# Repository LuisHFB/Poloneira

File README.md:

# Poloneira
Trabalho da esteira seletora de peças da aula de Acionamentos e Sensores, Prof. Leandro Poloni.

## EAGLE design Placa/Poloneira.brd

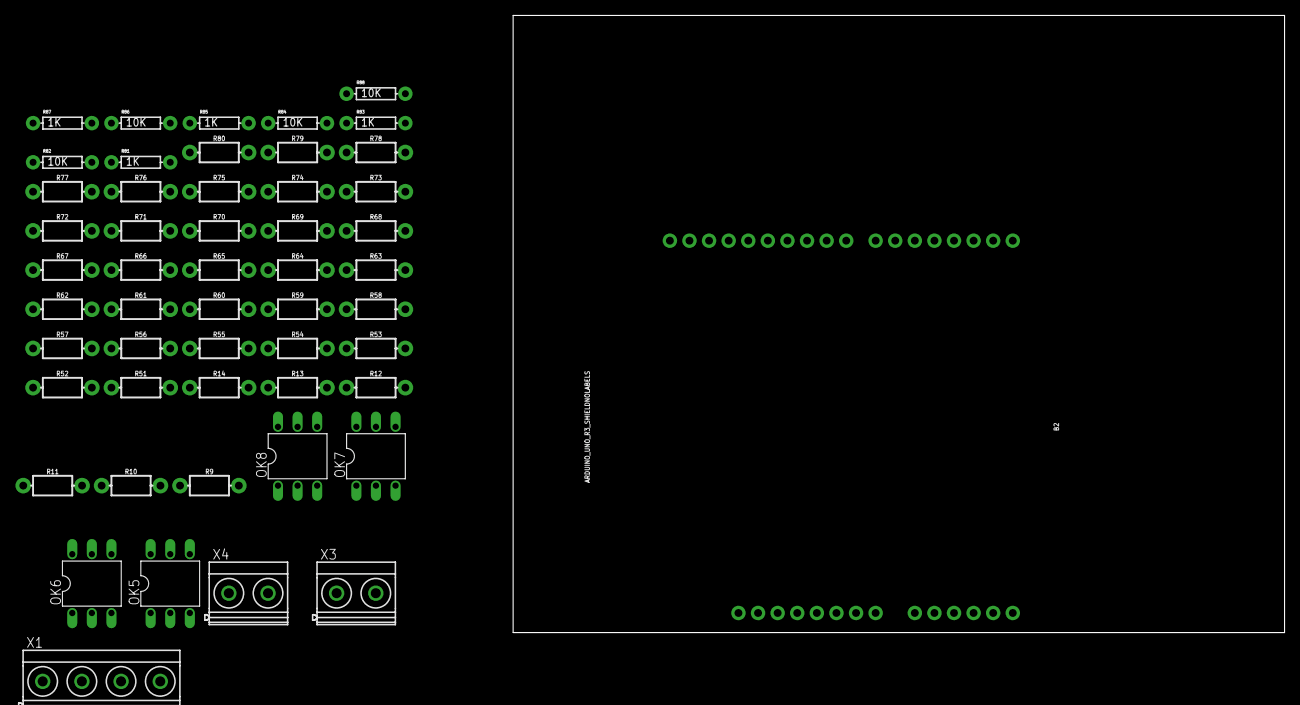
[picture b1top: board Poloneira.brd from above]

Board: 2 copper layers, 100.0 x 80.0 mm, 52 parts (0 on the bottom side), 15 nets, no tracks yet.

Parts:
B2: ARDUINO_UNO_R3_SHIELDNOLABELS; UNO_R3_SHIELD_NOLABELS
OK5, OK6, OK7, OK8: 4N25M; DIL06
R9, R10, R11, R12, R13, R14, R51, R52, R53, R54, R55, R56, R57, R58, R59, R60, R61, R62, R63, R64, R65, R66, R67, R68, R69, R70, R71, R72, R73, R74, R75, R76, R77, R78, R79, R80: AXIAL-0.3-KIT
R81, R83, R85, R87: 1K; AXIAL-0.3EZ
R82, R84, R86, R88: 10K; AXIAL-0.3EZ
X1: MKDSN1,5/4-5,08
X3, X4: MKDSN1,5/2-5,08

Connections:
+24V: R82.P$1, R84.P$1, R86.P$1, R88.P$1, X3.2
GND: OK5.2, OK5.4, OK6.2, OK6.4, OK7.2, OK7.4, OK8.2, OK8.4, R10.P$1, R12.P$1, R14.P$1, R52.P$1, R54.P$1, R56.P$1, R58.P$1, R60.P$1, R62.P$1, R64.P$1, R66.P$1, R68.P$1, R70.P$1, R72.P$1, R74.P$1, R76.P$1, R78.P$1, R80.P$1, X3.1, X4.2
unnamed: OK5.1, R81.P$1
unnamed: OK6.1, R83.P$1
unnamed: OK7.1, R85.P$1
unnamed: OK8.1, R87.P$1
unnamed: R81.P$2, R83.P$2, R85.P$2, R87.P$2
PISTAO1: OK5.5, R82.P$2, X1.1
PISTAO2: OK6.5, R84.P$2, X1.2
PISTAO3: OK7.5, R86.P$2, X1.3
PISTAO4: OK8.5, R88.P$2, X1.4
SENSA_5V: R13.P$2, R14.P$2
SENSB_5V: R9.P$2, R10.P$2, R51.P$2, R52.P$2, R53.P$2, R54.P$2, R55.P$2, R56.P$2, R57.P$2, R58.P$2, R59.P$2, R60.P$2, R61.P$2, R62.P$2, R63.P$2, R64.P$2, R65.P$2, R66.P$2, R67.P$2, R68.P$2, R69.P$2, R70.P$2, R71.P$2, R72.P$2, R73.P$2, R74.P$2, R75.P$2, R76.P$2, R77.P$2, R78.P$2, R79.P$2, R80.P$2
SENSB_24V: R9.P$1, R55.P$1, R57.P$1, R59.P$1, R61.P$1, R63.P$1, R65.P$1, R67.P$1, R69.P$1, R71.P$1, R73.P$1, R75.P$1, R77.P$1, R79.P$1
SENSM_5V: R11.P$2, R12.P$2

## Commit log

2018-10-31 Arquivos Eagle
    Arquivos BRD e SCH para placa
2018-11-06 05_11_2018
2018-11-09 09_11_2018
2018-11-09 09_11_2018_(2)
2018-11-12 12_11_2018_(1)
2018-11-12 Agora Funfa
2018-11-12 Agora sim

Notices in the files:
parts and their libraries:
SparkFun-Resistors: Licensing: Creative Commons ShareAlike 4.0 International - https://creativecommons.org/licenses/by-sa/4.0
